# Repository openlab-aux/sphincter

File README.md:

sphincter
=========
sphincter is the project name for an electronic door locking system designed at
and used by OpenLab Augsburg. This repo collects all parts of the project as 
there are
* the firmware running on the device (arduino + custom shield)
* a daemon that connects to the device via UART and exposes a HTTP API
* various client implementations
* other related files (e.g. PCB layourt for the shield, etc.)

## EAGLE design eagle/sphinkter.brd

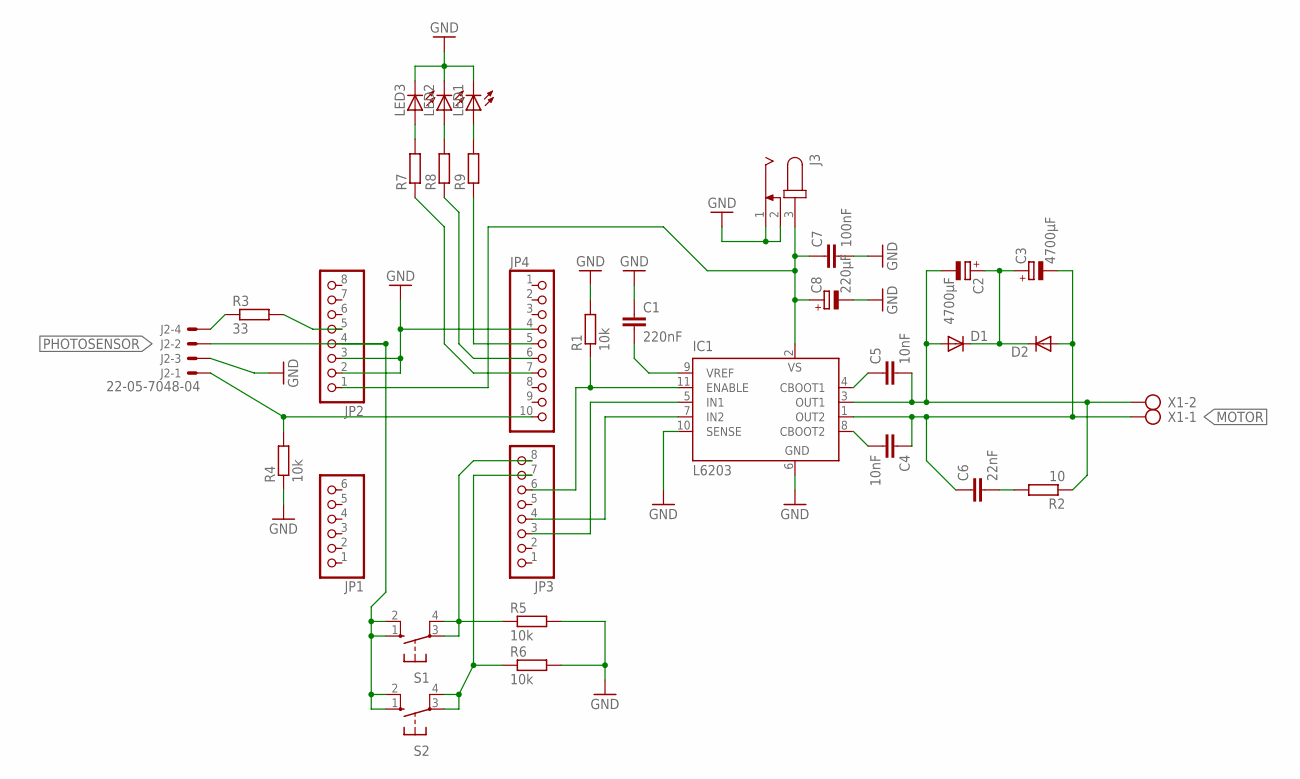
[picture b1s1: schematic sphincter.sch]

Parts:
C1: 220nF; C050-024X044
C2, C3: 4700µF; E7,5-16
C4, C5: 10nF; C025-025X050
C6: 22nF; C050-024X044
C7: 100nF; C050-024X044
C8: 220µF; E3,5-8
D1, D2: DIODE-DO27-15; DO27-15
IC1: L6203; MULTIWATT-11
J2: 22-05-7048-04; 7395-04
J3: JACK-PLUG0; SPC4077
JP1: PINHD-1X6; 1X06
JP2, JP3: PINHD-1X8; 1X08
JP4: PINHD-1X10; 1X10
LED1, LED2, LED3: LED5MM
R1, R4, R5, R6: 10k; 0207/10
R2: 10; 0207/10
R3: 33; 0207/10
R7, R8, R9: R-EU_0207/10; 0207/10
S1, S2: 10-XX; B3F-10XX
X1: AK500/2

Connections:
5V_DETECTOR: JP2.5, R3.2
GND: C1.1, C7.2, C8.-, IC1.6 (GND), IC1.10 (SENSE), J2.3, J3.1, J3.2, JP2.2, JP2.3, JP4.4, LED1.K (C), LED2.K (C), LED3.K (C), R1.2, R4.1, R5.2, R6.2
MOTOR: C3.-, C4.1, C6.1, D2.A, IC1.1 (OUT2), X1.1
unnamed: C1.2, IC1.9 (VREF)
unnamed: IC1.7 (IN2), JP3.4
unnamed: IC1.5 (IN1), JP3.3
unnamed: IC1.11 (ENABLE), JP3.6, R1.1
unnamed: C7.1, C8.+, IC1.2 (VS), J3.3, JP2.1
unnamed: C2.+, C3.+, D1.C, D2.C
unnamed: C4.2, IC1.8 (CBOOT2)
unnamed: C5.1, IC1.4 (CBOOT1)
unnamed: C6.2, R2.2
unnamed: C2.-, C5.2, D1.A, IC1.3 (OUT1), R2.1, X1.2
unnamed: JP3.8, R5.1, S1.3, S1.4 (P1)
unnamed: JP3.7, R6.1, S2.3, S2.4 (P1)
unnamed: JP4.5, R9.1
unnamed: LED3.A, R7.2
unnamed: LED2.A, R8.2
unnamed: LED1.A, R9.2
unnamed: JP4.6, R8.1
unnamed: JP4.7, R7.1
unnamed: J2.4, R3.1
PHOTOSENSOR: J2.2, JP2.4, S1.1 (S), S1.2 (S1), S2.1 (S), S2.2 (S1)
TO_ARDUINO: J2.1, JP4.10, R4.2

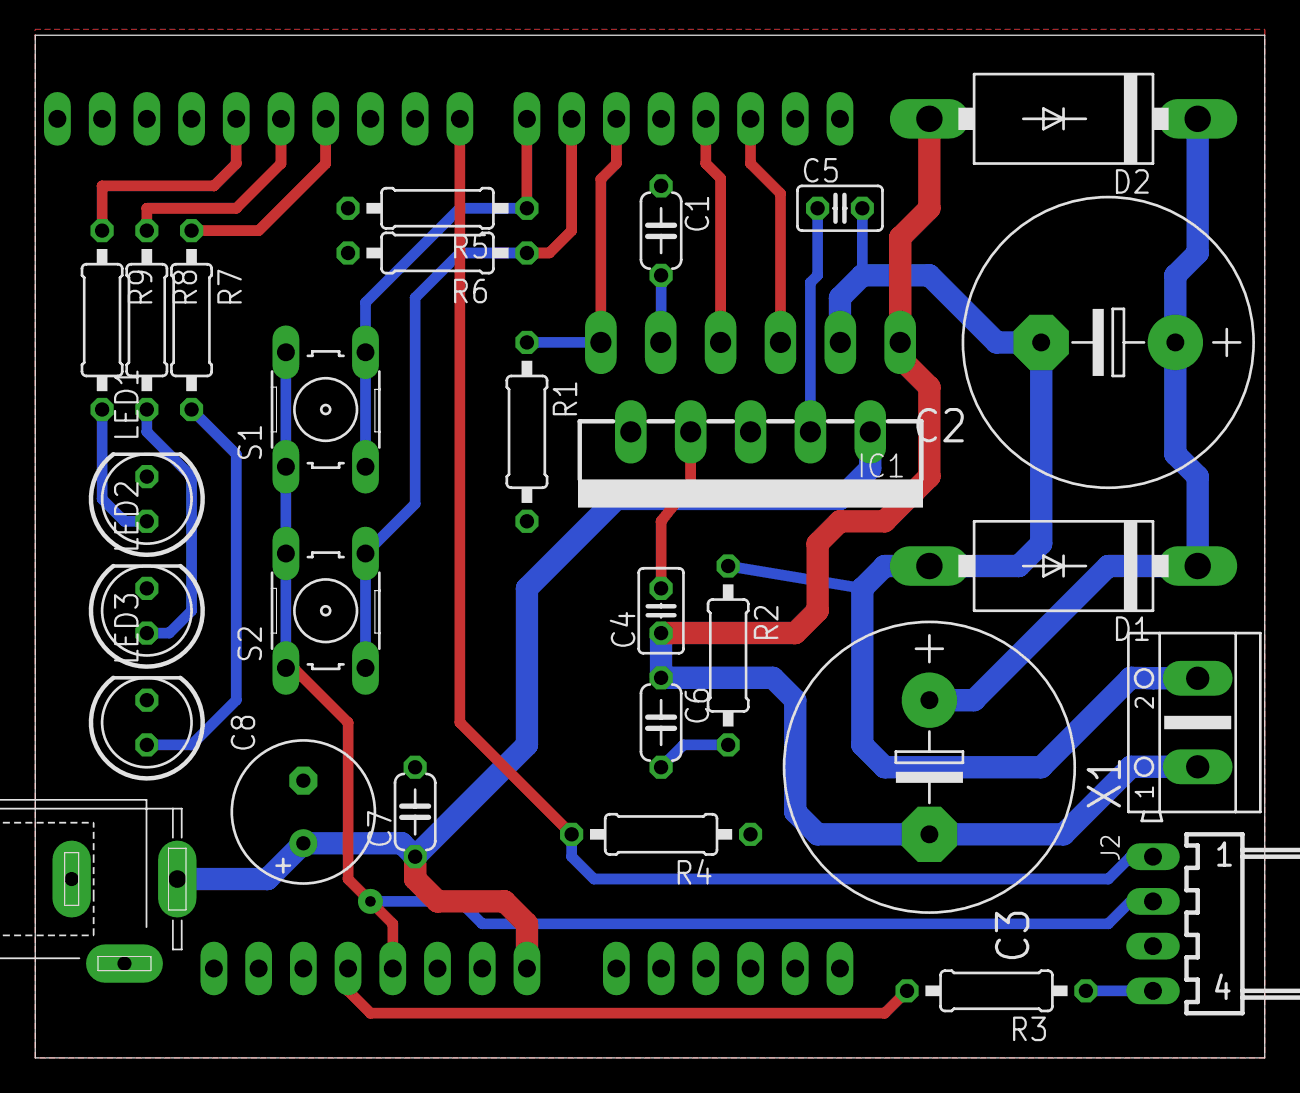
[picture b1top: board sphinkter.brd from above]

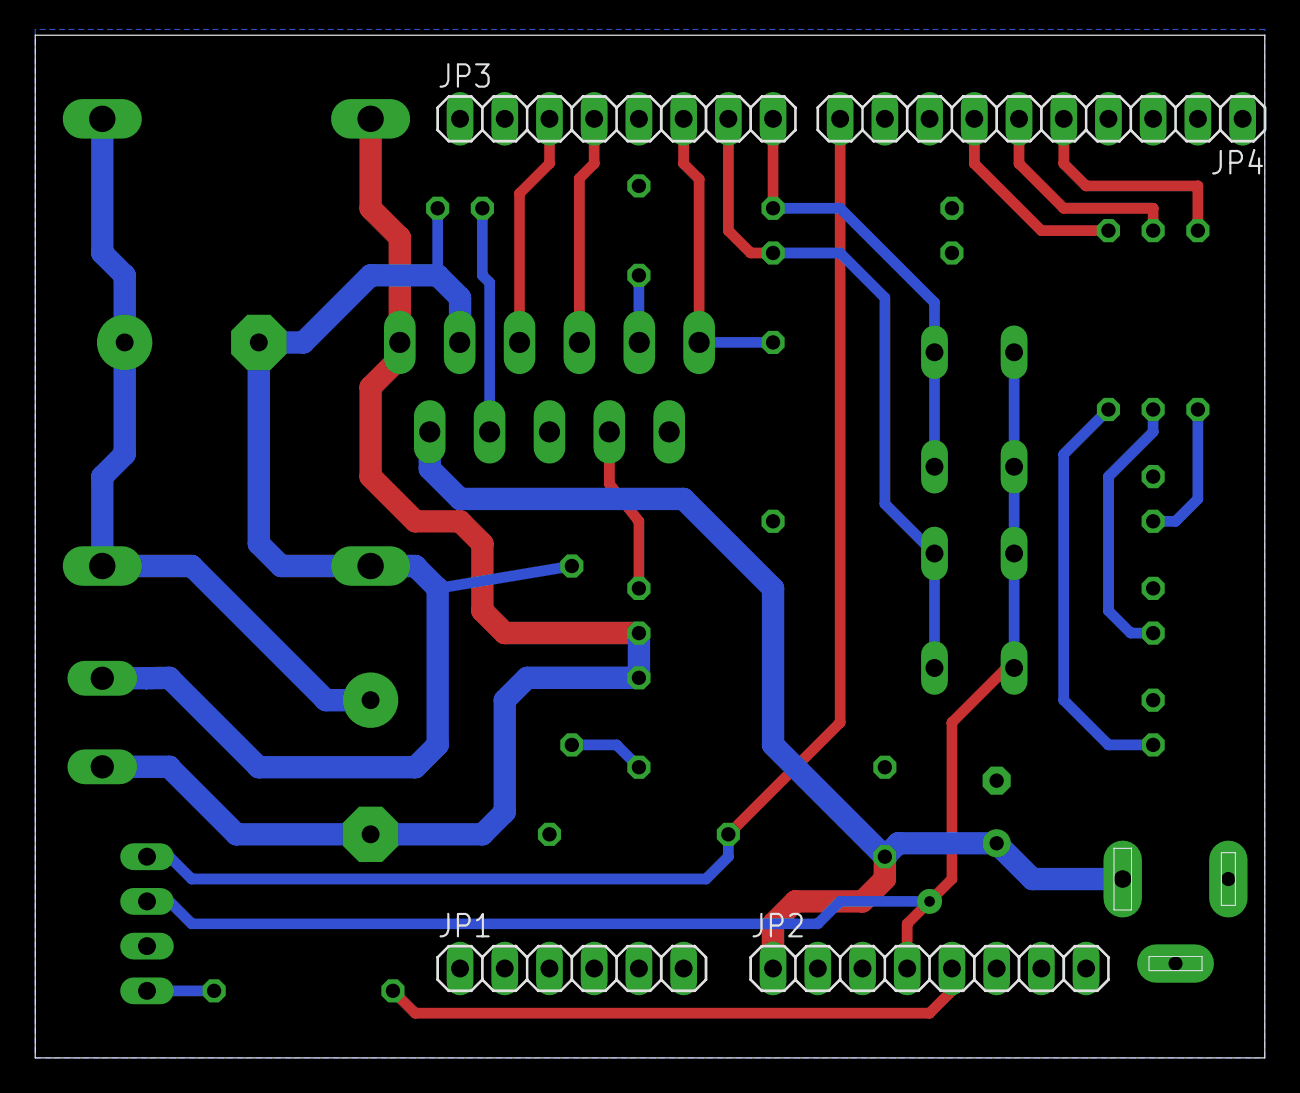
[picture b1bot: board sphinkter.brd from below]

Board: 2 copper layers, 69.8 x 58.1 mm, 32 parts (4 on the bottom side), 24 nets.

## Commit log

2014-01-11 added drehgeber drawing
2014-01-11 added network capability
2014-01-11 fixed counting
2014-01-12 another fix to avoid miscounting
2014-01-12 bad idea to delay before braking the motor
2014-01-14 added description in README.md
2014-01-17 changes to work with sphinkter board
    removed ethernet shield support
    added primitive serial communication
    implemented buttons and LEDs
    changed arduino pins
    other minor changes
2014-01-17 minor changes
2014-01-17 added eagle schematics and board layout
2014-01-17 reenabled reference drive on reset
2014-01-17 moar awesomeness
2014-01-17 added lib folder
2014-01-18 code cleanup
2014-01-20 add folder for arduino stuff
2014-01-20 added ino.ini
2014-01-20 changed 'shinkter' to 'sphincter'
2014-01-20 pretty printing
2014-01-20 initial commit for sphincter daemon
2014-01-21 added udev rule
    assign arduinos serial device to a fixed symlink
2014-01-21 changed rule to match the sphincter arduino board
2014-01-21 first daemon implementation under blue feeling
2014-01-21 faster reference :-)
2014-01-22 removed serial overhead
2014-01-22 consistent serial feedback
2014-01-22 fixed reference drive when door is open. Fixes #1
2014-01-22 serial device as created by the udev rule
2014-01-22 typo
2014-01-22 vacuuming and clean up
2014-01-27 pyhton version
2014-01-31 http auth
2014-01-31 added script for generating tokens
2014-02-08 fixes
2014-02-08 lichtschranke enprellt
2014-02-09 cleanup, comments
2014-02-19 adds reconnect on connection loss
2014-02-20 reimplemented serial handler class
    now reconnecting after connection loss should work
2014-02-20 adds exit if token file not found
2014-02-20 removes unnecessary underscores
2014-02-20 adds gentoken.py
2014-02-20 use config file for credentials
2014-02-20 use correct device
2014-02-20 generate links for the new token
2014-02-25 Added the current date to the generated e-mail.
2014-08-12 changes from labctl
2014-08-13 return fake sphincter state on action
2014-08-17 rm python daemon
2014-08-17 basic serial handler
2014-08-19 adds defines for serial responses
2014-08-19 send "ACK"
2014-08-19 adds protocol spec
2014-08-19 Update README.md
    add protocol spec
2014-08-20 basic http server that relays state from serial
2014-08-24 Handle multiple open HTTP requests. Testing.
    the daemon now waits for incoming serial data and responds to all open
    HTTP connections in the order in which they were received.
2014-08-24 channel pointer is unnecessary
2014-08-24 token authentication
2014-08-27 improved auth
    * only read file if it has changed
    * don´t use per hash salt
    * renaming
2014-08-27 talke mehr!
2014-08-27 changed serial response handling, still broken
2014-08-27 fixes, clean up, comments ...
2014-08-27 adds 'Enabled' field for hashes
2014-08-27 add delay for close button event (for leaving lab) (untested)
2014-08-29 release serial port before reconnecting
    otherwise we won't be able to connect on the same port again
2014-08-29 renaming
2014-08-29 err handling for sending serial data
2014-08-29 logging
2014-08-29 rebuilt http requests
    now it uses a single channel for all open http requests.
2014-08-29 detect a HTTP connection loss
    exit the blocking handler func
2014-08-29 call sphincter
2014-08-29 amends logging
2014-08-29 clean up, comments
2014-08-29 non blocking write on channel
2014-08-29 simple api calling
2014-08-30 adds TimerOne library
2014-08-31 ignore EOF
2014-08-31 hack avoiding misrouted responses
2014-09-03 func to toggle LEDs
2014-09-03 new button handling, fixes #8
2014-09-26 rm ACK response / add BUSY state
2014-09-26 seperate sphincter package, no requests on BUSY
    + blocking methods to open/close the door
    + State method
2014-09-26 use the new package, clean up, doc
2014-09-27 use flags
2014-09-27 adds simulator
2014-09-28 firmware: cleanup, edit/add doc-strings
2014-09-28 firmware: renames position constants
2014-09-28 daemon: return if door is already locked
2014-09-28 firmware: allways return state
2014-09-28 daemon: small fixes, cleanup
2014-09-28 daemon: set state "BUSY" in any case
    to avoid having more than one request in the small gap until
    sphincter returns "BUSY"
2014-09-28 daemon: adds reset request
2014-09-28 daemon: fix simulator
2014-09-29 firmware: adds timeout + failure response
2014-10-07 separate repo for firmware, re-add as submodule
2014-10-07 adds sphincter-remote as sumbmodule
2014-10-08 replaces daemon
    daemon --> daemon_deprecated
    new submodule: daemon
2014-10-08 update README
    adds image of sphincter
